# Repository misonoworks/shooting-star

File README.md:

# shooting-star
Alice-style 40% board with a big spacebar.

Shooting Star by ChromePcok in the MisonoWorks Discord

Shooting Star by MisonoWorks (hey that's me!)

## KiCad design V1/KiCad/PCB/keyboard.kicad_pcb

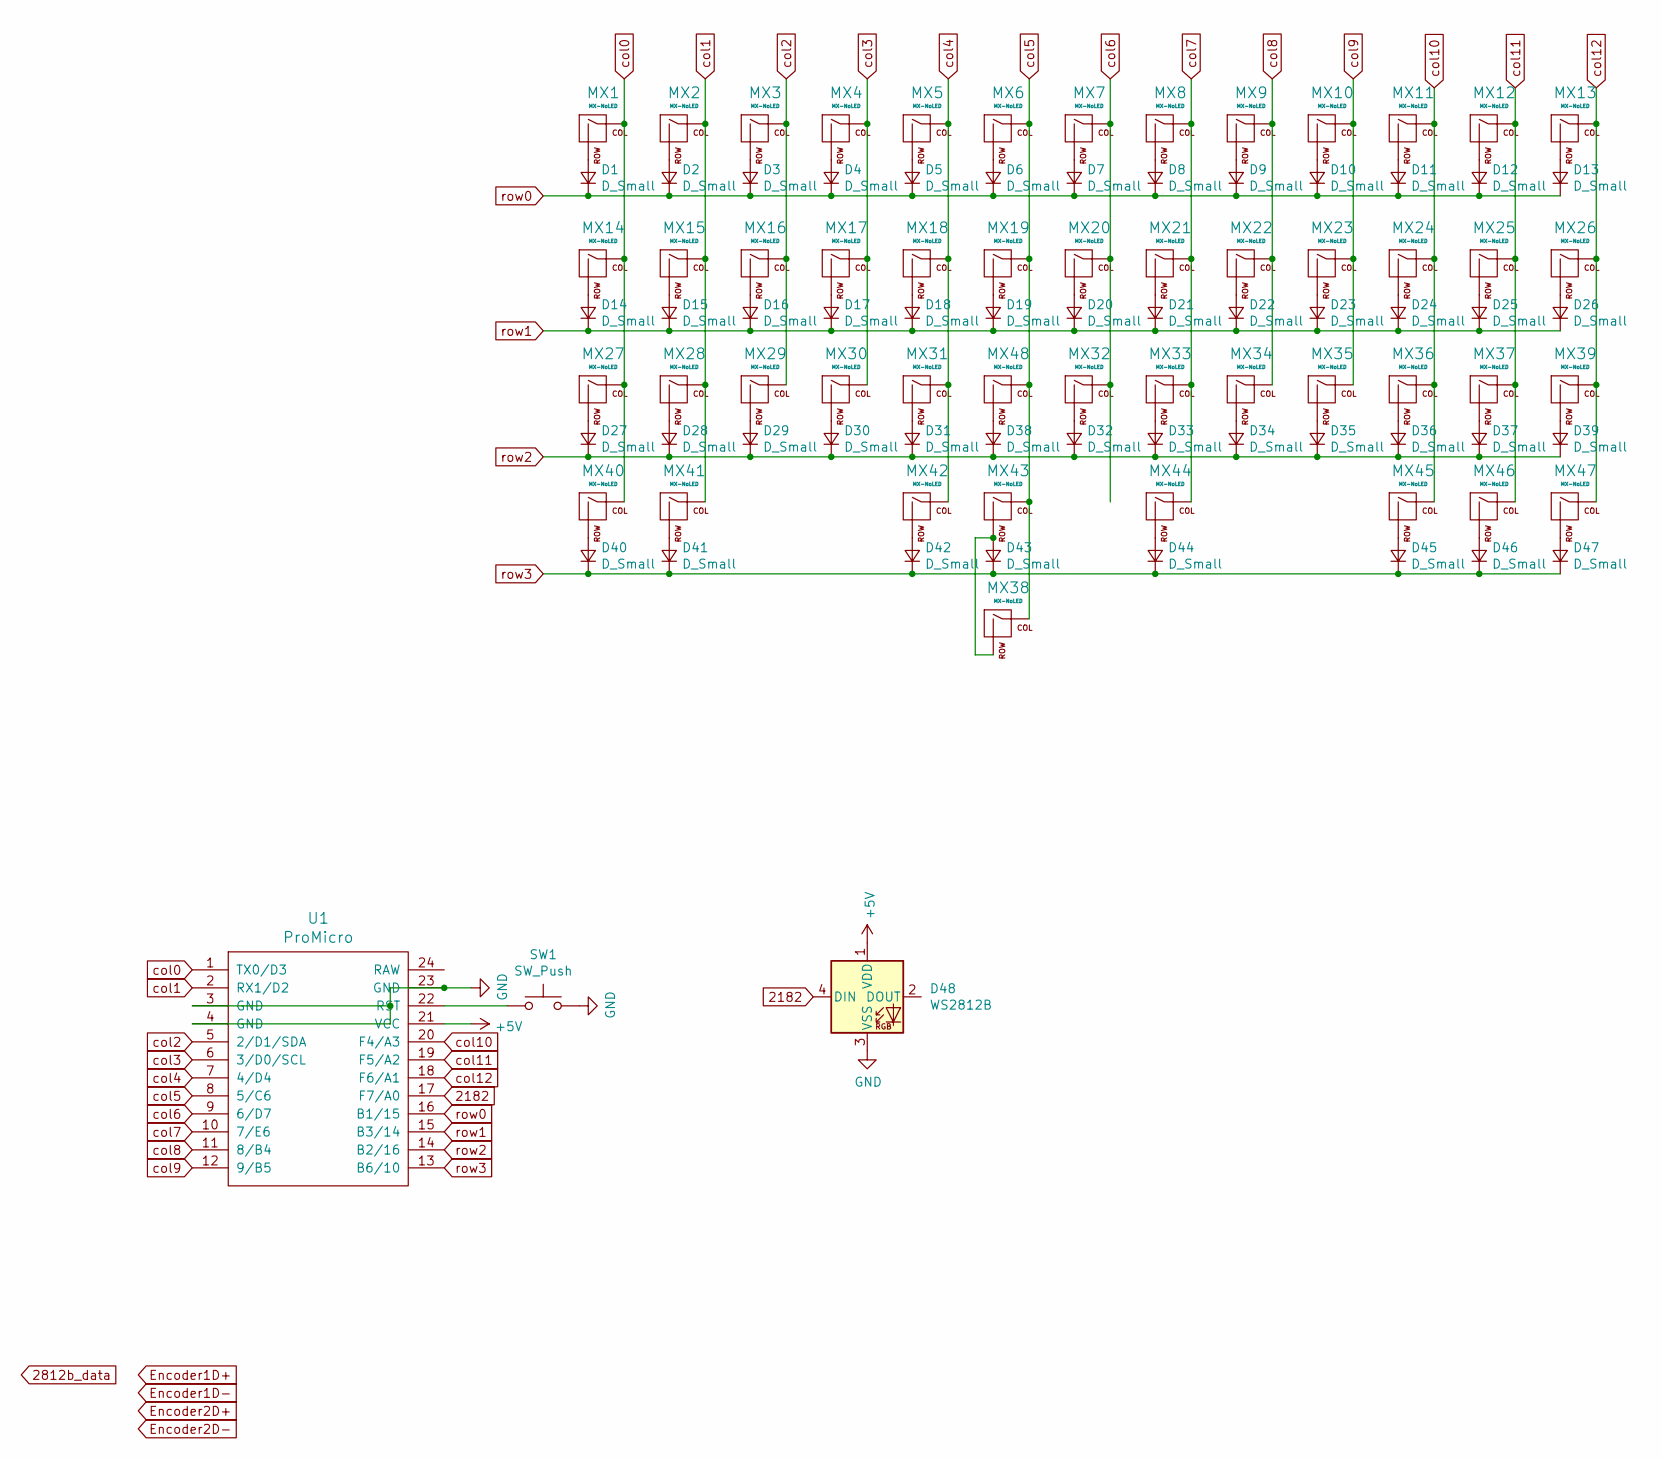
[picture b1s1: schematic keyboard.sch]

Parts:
D1, D2, D3, D4, D5, D6, D7, D8, D9, D10, D11, D12, D13, D14, D15, D16, D17, D18, D19, D20, D21, D22, D23, D24, D25, D26, D27, D28, D29, D30, D31, D32, D33, D34, D35, D36, D37, D38, D39, D40, D41, D42, D43, D44, D45, D46, D47: D_Small; D_DO-34_SOD68_P7.62mm_Horizontal
D48: WS2812B; LED_WS2812B_PLCC4_5.0x5.0mm_P3.2mm
MX1, MX2, MX3, MX4, MX5, MX6, MX7, MX8, MX9, MX10, MX11, MX12, MX15, MX16, MX17, MX18, MX19, MX20, MX21, MX22, MX23, MX24, MX25, MX28, MX29, MX30, MX31, MX32, MX33, MX34, MX35, MX36, MX37, MX48: MX-NoLED; MX-1U-NoLED
MX13, MX40: MX-NoLED; MX-1.5U-NoLED
MX14, MX26, MX41, MX45, MX46, MX47: MX-NoLED; MX-1.25U-NoLED
MX27, MX39: MX-NoLED; MX-1.75U-NoLED
MX38: MX-NoLED; MX-7U-ReversedStabilizers-NoLED
MX42, MX44: MX-NoLED; MX-2.25U-ReversedStabilizers-NoLED
MX43: MX-NoLED; MX-6.25U-ReversedStabilizers-NoLED
SW1: SW_Push; SKQG-1155865
U1: ProMicro; ProMicro_v3.5

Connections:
2182: D48.4 (DIN), U1.17 (F7/A0)
+5V: D48.1 (VDD), U1.21 (VCC)
GND: D48.3 (VSS), SW1.2, U1.3 (GND), U1.4 (GND), U1.23 (GND)
unnamed: D1.2 (A), MX1.2 (ROW)
unnamed: D2.2 (A), MX2.2 (ROW)
unnamed: D3.2 (A), MX3.2 (ROW)
unnamed: D4.2 (A), MX4.2 (ROW)
unnamed: D5.2 (A), MX5.2 (ROW)
unnamed: D6.2 (A), MX6.2 (ROW)
unnamed: D7.2 (A), MX7.2 (ROW)
unnamed: D8.2 (A), MX8.2 (ROW)
unnamed: D9.2 (A), MX9.2 (ROW)
unnamed: D10.2 (A), MX10.2 (ROW)
unnamed: D11.2 (A), MX11.2 (ROW)
unnamed: D12.2 (A), MX12.2 (ROW)
unnamed: D13.2 (A), MX13.2 (ROW)
unnamed: D14.2 (A), MX14.2 (ROW)
unnamed: D15.2 (A), MX15.2 (ROW)
unnamed: D16.2 (A), MX16.2 (ROW)
unnamed: D17.2 (A), MX17.2 (ROW)
unnamed: D18.2 (A), MX18.2 (ROW)
unnamed: D19.2 (A), MX19.2 (ROW)
unnamed: D20.2 (A), MX20.2 (ROW)
unnamed: D21.2 (A), MX21.2 (ROW)
unnamed: D22.2 (A), MX22.2 (ROW)
unnamed: D23.2 (A), MX23.2 (ROW)
unnamed: D24.2 (A), MX24.2 (ROW)
unnamed: D25.2 (A), MX25.2 (ROW)
unnamed: D26.2 (A), MX26.2 (ROW)
unnamed: D27.2 (A), MX27.2 (ROW)
unnamed: D28.2 (A), MX28.2 (ROW)
unnamed: D29.2 (A), MX29.2 (ROW)
unnamed: D30.2 (A), MX30.2 (ROW)
unnamed: D31.2 (A), MX31.2 (ROW)
unnamed: D32.2 (A), MX32.2 (ROW)
unnamed: D33.2 (A), MX33.2 (ROW)
unnamed: D34.2 (A), MX34.2 (ROW)
unnamed: D35.2 (A), MX35.2 (ROW)
unnamed: D36.2 (A), MX36.2 (ROW)
unnamed: D37.2 (A), MX37.2 (ROW)
unnamed: D38.2 (A), MX48.2 (ROW)
unnamed: D39.2 (A), MX39.2 (ROW)
unnamed: D40.2 (A), MX40.2 (ROW)
unnamed: D41.2 (A), MX41.2 (ROW)
unnamed: D42.2 (A), MX42.2 (ROW)
unnamed: D43.2 (A), MX38.2 (ROW), MX43.2 (ROW)
unnamed: D44.2 (A), MX44.2 (ROW)
unnamed: D45.2 (A), MX45.2 (ROW)
unnamed: D46.2 (A), MX46.2 (ROW)
unnamed: D47.2 (A), MX47.2 (ROW)
unnamed: SW1.1, U1.22 (RST)
col0: MX1.1 (COL), MX14.1 (COL), MX27.1 (COL), MX40.1 (COL), U1.1 (TX0/D3)
col1: MX2.1 (COL), MX15.1 (COL), MX28.1 (COL), MX41.1 (COL), U1.2 (RX1/D2)
col2: MX3.1 (COL), MX16.1 (COL), MX29.1 (COL), U1.5 (2/D1/SDA)
col3: MX4.1 (COL), MX17.1 (COL), MX30.1 (COL), U1.6 (3/D0/SCL)
col4: MX5.1 (COL), MX18.1 (COL), MX31.1 (COL), MX42.1 (COL), U1.7 (4/D4)
col5: MX6.1 (COL), MX19.1 (COL), MX38.1 (COL), MX43.1 (COL), MX48.1 (COL), U1.8 (5/C6)
col6: MX7.1 (COL), MX20.1 (COL), MX32.1 (COL), U1.9 (6/D7)
col7: MX8.1 (COL), MX21.1 (COL), MX33.1 (COL), MX44.1 (COL), U1.10 (7/E6)
col8: MX9.1 (COL), MX22.1 (COL), MX34.1 (COL), U1.11 (8/B4)
col9: MX10.1 (COL), MX23.1 (COL), MX35.1 (COL), U1.12 (9/B5)
col10: MX11.1 (COL), MX24.1 (COL), MX36.1 (COL), MX45.1 (COL), U1.20 (F4/A3)
col11: MX12.1 (COL), MX25.1 (COL), MX37.1 (COL), MX46.1 (COL), U1.19 (F5/A2)
col12: MX13.1 (COL), MX26.1 (COL), MX39.1 (COL), MX47.1 (COL), U1.18 (F6/A1)
row0: D1.1 (K), D2.1 (K), D3.1 (K), D4.1 (K), D5.1 (K), D6.1 (K), D7.1 (K), D8.1 (K), D9.1 (K), D10.1 (K), D11.1 (K), D12.1 (K), D13.1 (K), U1.16 (B1/15)
row1: D14.1 (K), D15.1 (K), D16.1 (K), D17.1 (K), D18.1 (K), D19.1 (K), D20.1 (K), D21.1 (K), D22.1 (K), D23.1 (K), D24.1 (K), D25.1 (K), D26.1 (K), U1.15 (B3/14)
row2: D27.1 (K), D28.1 (K), D29.1 (K), D30.1 (K), D31.1 (K), D32.1 (K), D33.1 (K), D34.1 (K), D35.1 (K), D36.1 (K), D37.1 (K), D38.1 (K), D39.1 (K), U1.14 (B2/16)
row3: D40.1 (K), D41.1 (K), D42.1 (K), D43.1 (K), D44.1 (K), D45.1 (K), D46.1 (K), D47.1 (K), U1.13 (B6/10)

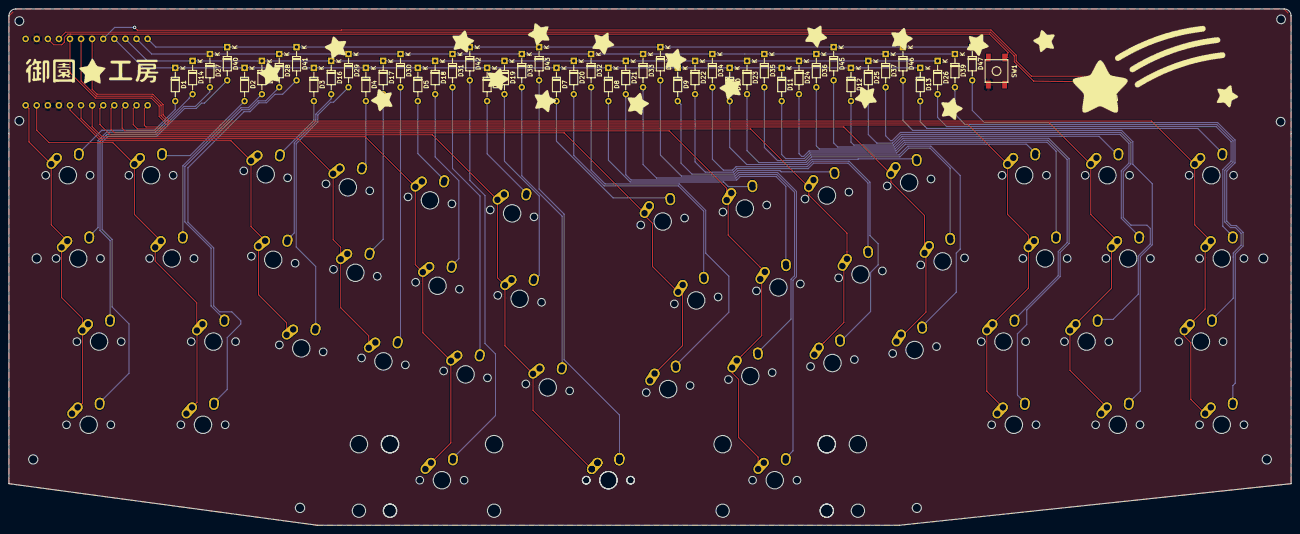
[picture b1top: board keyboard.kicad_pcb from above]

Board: 2 copper layers, 293.7 x 118.3 mm, 98 parts (1 on the bottom side), 68 nets.
